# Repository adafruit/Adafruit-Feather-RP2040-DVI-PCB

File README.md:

## Adafruit Feather RP2040 DVI PCB

<a href="http://www.adafruit.com/products/5710"><br/>
Click here to purchase one from the Adafruit shop</a>

PCB files for the Adafruit Feather RP2040 DVI. 

Format is EagleCAD schematic and board layout
* https://www.adafruit.com/product/5710

### Description

Wouldn't it be cool if you could display images and graphics from a microcontroller directly to an HDMI monitor or television? We think so! So we designed this RP2040 Feather that has a digital video output (a.k.a DVI) that will work with any HDMI monitor or display. Note it doesn't do audio, just graphics!

It's kinda like we took our RP2040 Feather and DVI Breakout board and glued them together. You get all the pins for use on the Feather, the Lipoly battery support, USB C power / data, onboard NeoPixel, 8MB of FLASH for storing code and files, and then with the 8 unused pins, a DVI output that can be used with the PicoDVI library in Arduino or Pico SDK (note we don't have Circuitpython support for DVI output at this time)

In Arduino, which is what we recommend, we use our fork of PicoDVI to create an internal framebuffer of 320x240 or 400x240 16-bit pixels that is then continuously blitted out as pixel-doubled 640x480 or 800x480 digital video. Whatever you 'draw' to the internal memory framebuffer appears instantly on the digital display in crisp color. Since the library is a subclass of AdafruitGFX, it'll be familiar to folks who have used our TFT or OLED displays before.

Note that the DVI video generation uses one full core, both PIOs, and 150K (320x240) or 190K (400x240) of SRAM. It's kinda maxed out so be aware of the remaining resource limitations.

We also connected the HDMI-connectors I2C pins to the SDA/SCL of the Feather (through a safe level shifter) so you can read the EDID EEPROM of displays, and have broken out the CEC and Utility pads. The Hot Plug Detect pin is also available on the very end of the 16-pin header. Read this pin to know when a display has been connected!

### License

Adafruit invests time and resources providing this open source design, please support Adafruit and open-source hardware by purchasing products from [Adafruit](https://www.adafruit.com)!

Designed by Limor Fried/Ladyada for Adafruit Industries.

Creative Commons Attribution/Share-Alike, all text above must be included in any redistribution. 
See license.txt for additional details.

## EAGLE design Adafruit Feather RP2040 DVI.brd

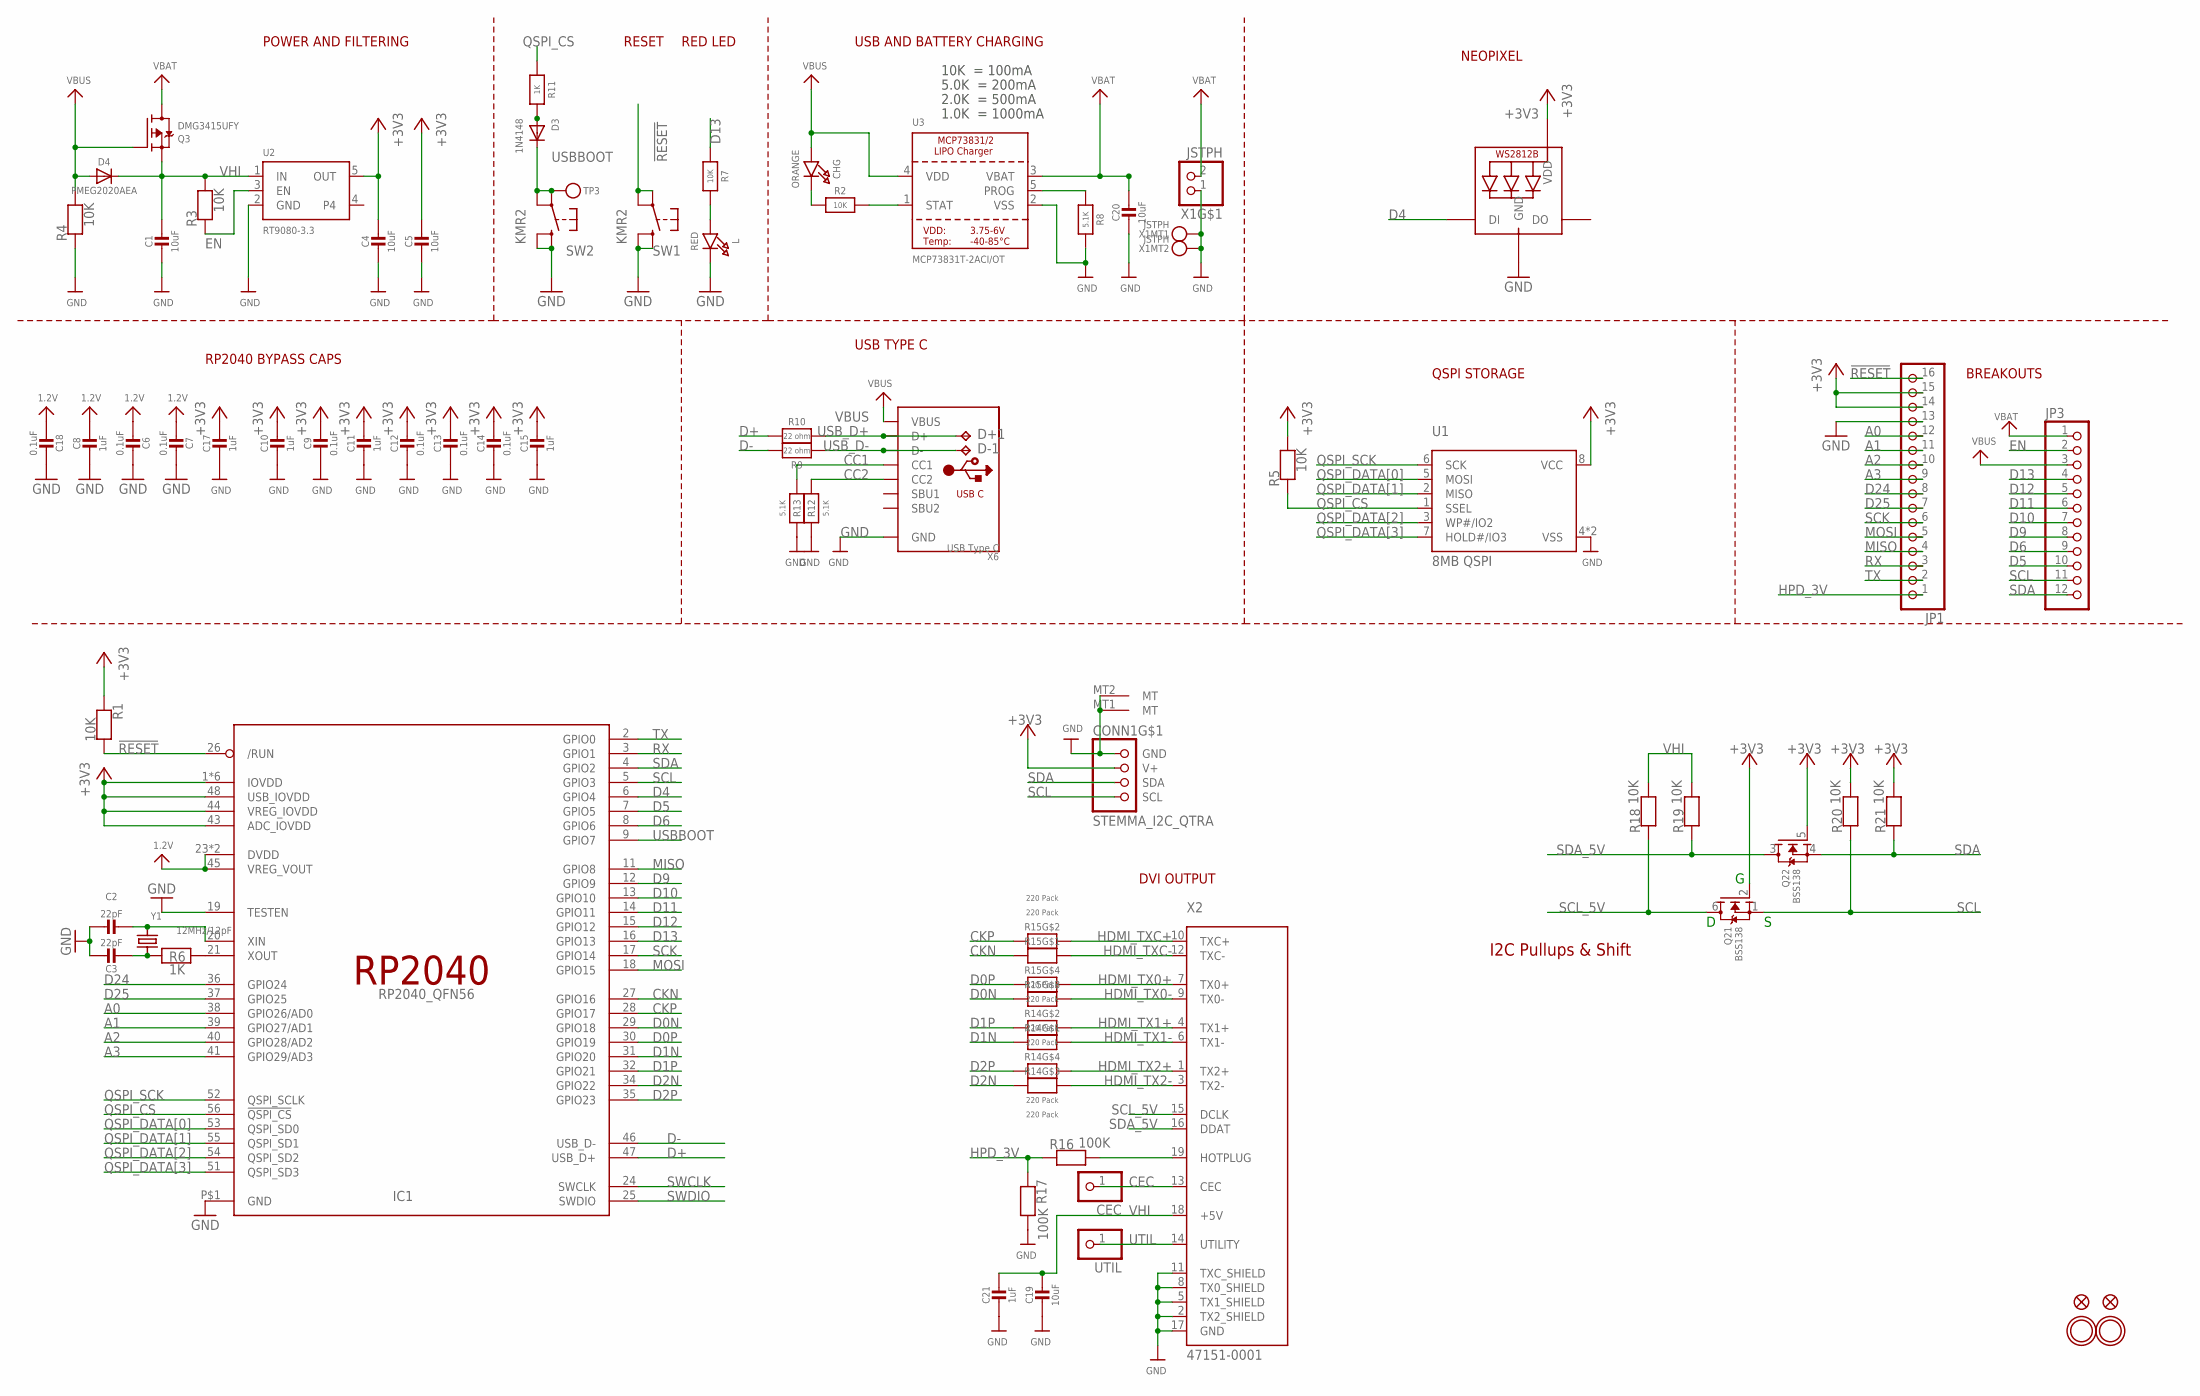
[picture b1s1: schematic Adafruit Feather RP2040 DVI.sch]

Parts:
C1, C4, C5, C19, C20: 10uF; 0805-NO
C2, C3: 22pF; _0402NO
C6, C7, C9, C12, C13, C14, C18: 0.1uF; _0402NO
C8, C10, C11, C15, C17, C21: 1uF; _0402NO
CEC: HEADER-1X1ROUND; 1X01_ROUND
CHG: ORANGE; CHIPLED_0603_NOOUTLINE
CONN1: STEMMA_I2C_QTRA; JST_SH4_RA
D3: 1N4148; SOD-323F
D4: PMEG2020AEA; SOD-323F
D+1: TPB1,27; B1,27
D-1: TPB1,27; B1,27
IC1: RP2040_QFN56; QFN56_7MM_REDUCEDEPAD
JP1: HEADER-1X16ROUND; 1X16_ROUND
JP3: HEADER-1X12; 1X12_ROUND
L: RED; CHIPLED_0603_NOOUTLINE
LED1: WS2812B_SK6805_1515; SK6805_1515
Q2: BSS138; SOT363
Q3: DMG3415UFY; DFN2015-3
R1, R2, R3, R4, R5, R7, R18, R19, R20, R21: 10K; _0402NO
R6, R11: 1K; _0402NO
R8, R12, R13: 5.1K; _0402NO
R9, R10: 22 ohm; _0402NO
R14, R15: 220 Pack; RESPACK_4X0603
R16, R17: 100K; _0402NO
SW1, SW2: KMR2; BTN_RKB2_4.6X2.8
TP3: TESTPOINTROUND1.5MMNO; TESTPOINT_ROUND_1.5MM_NO
U1: 8MB QSPI; USON8_4X4
U2: RT9080-3.3; SOT23-5; JLC_ROTATION 0
U3: MCP73831T-2ACI/OT; SOT23-5
U$31, U$32: MOUNTINGHOLE2.5; MOUNTINGHOLE_2.5_PLATED
U$34, U$35: FIDUCIAL_1MM
UTIL: HEADER-1X1ROUND; 1X01_ROUND
X1: JSTPH; JSTPH2_BATT
X2: 47151-0001; HDMI_MOLEX_47151-0001
X6: USB Type C; USB_C_CUSB31-CFM2AX-01-X
Y1: 12MHz/12pF; CRYSTAL_2.5X2

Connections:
1.2V: C6.2, C7.2, C8.1, C18.2, IC1.23 (DVDD), IC1.45 (VREG_VOUT), IC1.50 (DVDD)
!RESET: IC1.26 (/RUN), JP1.16, R1.2, SW1.A, SW1.A' (P1)
+3V3: C4.1, C5.1, C9.1, C10.1, C11.1, C12.1, C13.1, C14.1, C15.1, C17.1, CONN1.2 (V+), IC1.1 (IOVDD), IC1.10 (IOVDD), IC1.22 (IOVDD), IC1.33 (IOVDD), IC1.42 (IOVDD), IC1.43 (ADC_IOVDD), IC1.44 (VREG_IOVDD), IC1.48 (USB_IOVDD), IC1.49 (IOVDD), JP1.14, JP1.15, LED1.2 (VDD), Q2.2 (G), Q2.5 (G), R1.1, R5.2, R20.2, R21.2, U1.8 (VCC), U2.5 (OUT)
A0: IC1.38 (GPIO26/AD0), JP1.12
A1: IC1.39 (GPIO27/AD1), JP1.11
A2: IC1.40 (GPIO28/AD2), JP1.10
A3: IC1.41 (GPIO29/AD3), JP1.9
CC1: R13.2, X6.A5 (CC1)
CC2: R12.2, X6.B5 (CC2)
CEC: CEC.1, X2.13 (CEC)
CKN: IC1.27 (GPIO16), R15.8 (2)
CKP: IC1.28 (GPIO17), R15.7 (2)
D0N: IC1.29 (GPIO18), R15.6 (2)
D0P: IC1.30 (GPIO19), R15.5 (2)
D1N: IC1.31 (GPIO20), R14.8 (2)
D1P: IC1.32 (GPIO21), R14.7 (2)
D2N: IC1.34 (GPIO22), R14.6 (2)
D2P: IC1.35 (GPIO23), R14.5 (2)
D4: IC1.6 (GPIO4), LED1.1 (DI)
D5: IC1.7 (GPIO5), JP3.10
D6: IC1.8 (GPIO6), JP3.9
D9: IC1.12 (GPIO9), JP3.8
D10: IC1.13 (GPIO10), JP3.7
D11: IC1.14 (GPIO11), JP3.6
D12: IC1.15 (GPIO12), JP3.5
D13: IC1.16 (GPIO13), JP3.4, R7.1
D24: IC1.36 (GPIO24), JP1.8
D25: IC1.37 (GPIO25), JP1.7
D+: IC1.47 (USB_D+), R10.2
D-: IC1.46 (USB_D-), R9.2
EN: JP3.2, R3.1, U2.3 (EN)
GND: C1.2, C2.1, C3.1, C4.2, C5.2, C6.1, C7.1, C8.2, C9.2, C10.2, C11.2, C12.2, C13.2, C14.2, C15.2, C17.2, C18.1, C19.2, C20.2, C21.2, CONN1.1 (GND), CONN1.MT1 (MT), CONN1.MT2 (MT), IC1.19 (TESTEN), IC1.P$1 (GND), JP1.13, L.C, LED1.4 (GND), R4.1, R8.2, R12.1, R13.1, R17.2, SW1.B (S), SW1.B' (S1), SW2.B (S), SW2.B' (S1), U1.4 (VSS), U1.PAD (VSS), U2.2 (GND), U3.2 (VSS), X1.1, X1.NC1, X1.NC2, X2.2 (TX2_SHIELD), X2.5 (TX1_SHIELD), X2.8 (TX0_SHIELD), X2.11 (TXC_SHIELD), X2.17 (GND), X2.P$1 (GND), X2.P$2 (GND), X2.P$3 (GND), X2.P$4 (GND), X6.A1B12 (GND), X6.B1A12 (GND)
HDMI_TX0+: R15.4 (1), X2.7 (TX0+)
HDMI_TX0-: R15.3 (1), X2.9 (TX0-)
HDMI_TX1+: R14.2 (1), X2.4 (TX1+)
HDMI_TX1-: R14.1, X2.6 (TX1-)
HDMI_TX2+: R14.4 (1), X2.1 (TX2+)
HDMI_TX2-: R14.3 (1), X2.3 (TX2-)
HDMI_TXC+: R15.2 (1), X2.10 (TXC+)
HDMI_TXC-: R15.1, X2.12 (TXC-)
HPD: R16.2, X2.19 (HOTPLUG)
HPD_3V: JP1.1, R16.1, R17.1
MISO: IC1.11 (GPIO8), JP1.4
MOSI: IC1.18 (GPIO15), JP1.5
unnamed: CHG.C, R2.1
unnamed: L.A, R7.2
unnamed: R2.2, U3.1 (STAT)
unnamed: R8.1, U3.5 (PROG)
unnamed: C2.2, IC1.20 (XIN), Y1.3 (2)
unnamed: C3.2, R6.1, Y1.1
unnamed: IC1.21 (XOUT), R6.2
unnamed: D3.A, R11.2
QSPI_CS: IC1.56 (!QSPI_CS), R5.1, R11.1, U1.1 (SSEL)
QSPI_DATA[0]: IC1.53 (QSPI_SD0), U1.5 (MOSI)
QSPI_DATA[1]: IC1.55 (QSPI_SD1), U1.2 (MISO)
QSPI_DATA[2]: IC1.54 (QSPI_SD2), U1.3 (WP#/IO2)
QSPI_DATA[3]: IC1.51 (QSPI_SD3), U1.7 (HOLD#/IO3)
QSPI_SCK: IC1.52 (QSPI_SCLK), U1.6 (SCK)
RX: IC1.3 (GPIO1), JP1.3
SCK: IC1.17 (GPIO14), JP1.6
SCL: CONN1.4 (SCL), IC1.5 (GPIO3), JP3.11, Q2.1 (S), R20.1
SCL_5V: Q2.6 (D), R18.1, X2.15 (DCLK)
SDA: CONN1.3 (SDA), IC1.4 (GPIO2), JP3.12, Q2.4 (S), R21.1
SDA_5V: Q2.3 (D), R19.1, X2.16 (DDAT)
SWCLK: IC1.24 (SWCLK)
SWDIO: IC1.25 (SWDIO)
TX: IC1.2 (GPIO0), JP1.2
USBBOOT: D3.C, IC1.9 (GPIO7), SW2.A, SW2.A' (P1), TP3.P$1
USB_D+: D+1.TP, R10.1, X6.A6 (D+), X6.B6 (D+)
USB_D-: D-1.TP, R9.1, X6.A7 (D-), X6.B7 (D-)
UTIL: UTIL.1, X2.14 (UTILITY)
VBAT: C20.1, JP3.1, Q3.3 (D), U3.3 (VBAT), X1.2
VBUS: CHG.A, D4.A, JP3.3, Q3.1 (G), R4.2, U3.4 (VDD), X6.A4B9 (VBUS), X6.B4A9 (VBUS)
VHI: C1.1, C19.1, C21.1, D4.C, Q3.2 (S), R3.2, R18.2, R19.2, U2.1 (IN), X2.18 (+5V)

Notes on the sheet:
POWER AND FILTERING
RESET
10K = 100mA
5.0K = 200mA
2.0K = 500mA
1.0K = 1000mA
USB AND BATTERY CHARGING
BREAKOUTS
RED LED
DVI OUTPUT
RP2040 BYPASS CAPS
USB TYPE C
QSPI STORAGE
NEOPIXEL
I2C Pullups & Shift

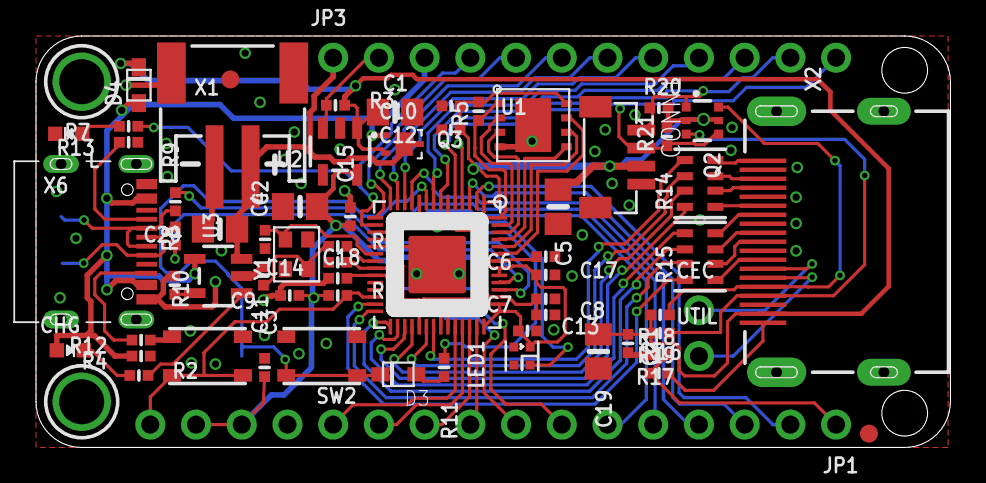
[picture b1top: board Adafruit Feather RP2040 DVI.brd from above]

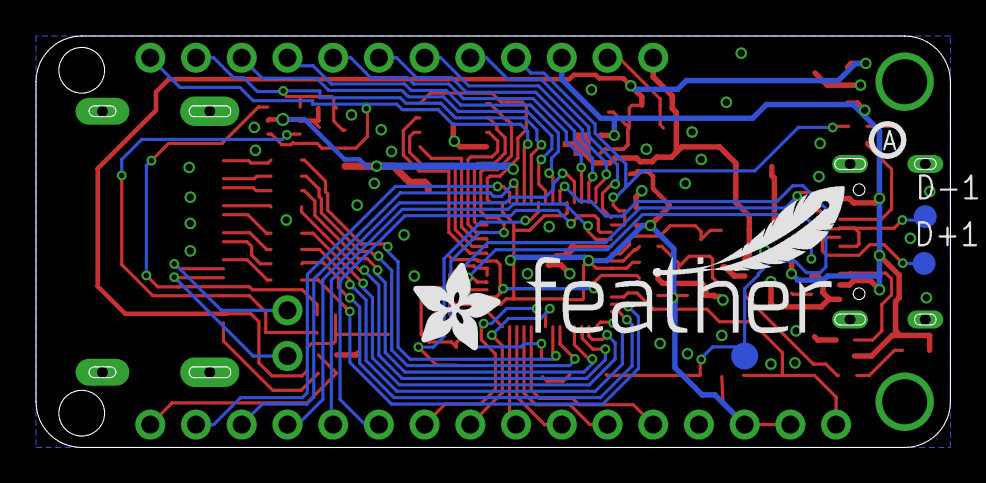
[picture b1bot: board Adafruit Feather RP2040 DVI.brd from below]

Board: 2 copper layers, 50.8 x 22.9 mm, 141 parts (38 on the bottom side), 72 nets.

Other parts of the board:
PLABEL0: PLABEL0
PLABEL1: PLABEL1
PLABEL2: PLABEL2
PLABEL3: PLABEL3
PLABEL4: PLABEL4
PLABEL5: PLABEL5
PLABEL6: PLABEL6
PLABEL7: PLABEL7
PLABEL8: PLABEL8
PLABEL9: PLABEL9
PLABEL10: PLABEL10
PLABEL11: PLABEL11
PLABEL12: PLABEL12
PLABEL13: PLABEL13
PLABEL14: PLABEL14
PLABEL15: PLABEL15
PLABEL16: PLABEL16
PLABEL17: PLABEL17
PLABEL18: PLABEL18
PLABEL19: PLABEL19
PLABEL20: PLABEL20
PLABEL21: PLABEL21
PLABEL22: PLABEL22
PLABEL23: PLABEL23
PLABEL24: PLABEL24
PLABEL25: PLABEL25
PLABEL26: PLABEL26
PLABEL27: PLABEL27
PLABEL28: PLABEL28
PLABEL29: PLABEL29
PLABEL30: PLABEL30
PLABEL31: PLABEL31
PLABEL32: PLABEL32
PLABEL33: PLABEL33
PLABEL34: PLABEL34
PLABEL35: PLABEL35
PLABEL36: PLABEL36
PLABEL37: PLABEL37
PLABEL38: PLABEL38
PLABEL39: PLABEL39
PLABEL40: PLABEL40
PLABEL41: PLABEL41
PLABEL42: PLABEL42
PLABEL43: PLABEL43
PLABEL44: PLABEL44
PLABEL45: PLABEL45
PLABEL46: PLABEL46
PLABEL47: PLABEL47
PLABEL48: PLABEL48
PLABEL49: PLABEL49
PLABEL50: PLABEL50
PLABEL51: PLABEL51
PLABEL52: PLABEL52
PLABEL53: PLABEL53
PLABEL54: PLABEL54
PLABEL55: PLABEL55
PLABEL56: PLABEL56
PLABEL57: PLABEL57
PLABEL58: PLABEL58
PLABEL59: PLABEL59
PLABEL60: PLABEL60
PLABEL61: PLABEL61
PLABEL62: PLABEL62
PLABEL63: PLABEL63
PLABEL64: PLABEL64
PLABEL65: PLABEL65
PLABEL66: PLABEL66
PLABEL67: PLABEL67
U$13: PCBFEAT-REV-040
U$42: FEATHERLOGO_MED
U$46: ADAFRUIT_5MM

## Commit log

2023-03-23 Add board files.
2023-03-23 Add PrettyPins.
2023-05-30 Add factory reset file.

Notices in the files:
parts and their libraries:
microbuilder: This work is placed in the public domain, and may be freely used for commercial and non-commercial work with the following conditions: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
